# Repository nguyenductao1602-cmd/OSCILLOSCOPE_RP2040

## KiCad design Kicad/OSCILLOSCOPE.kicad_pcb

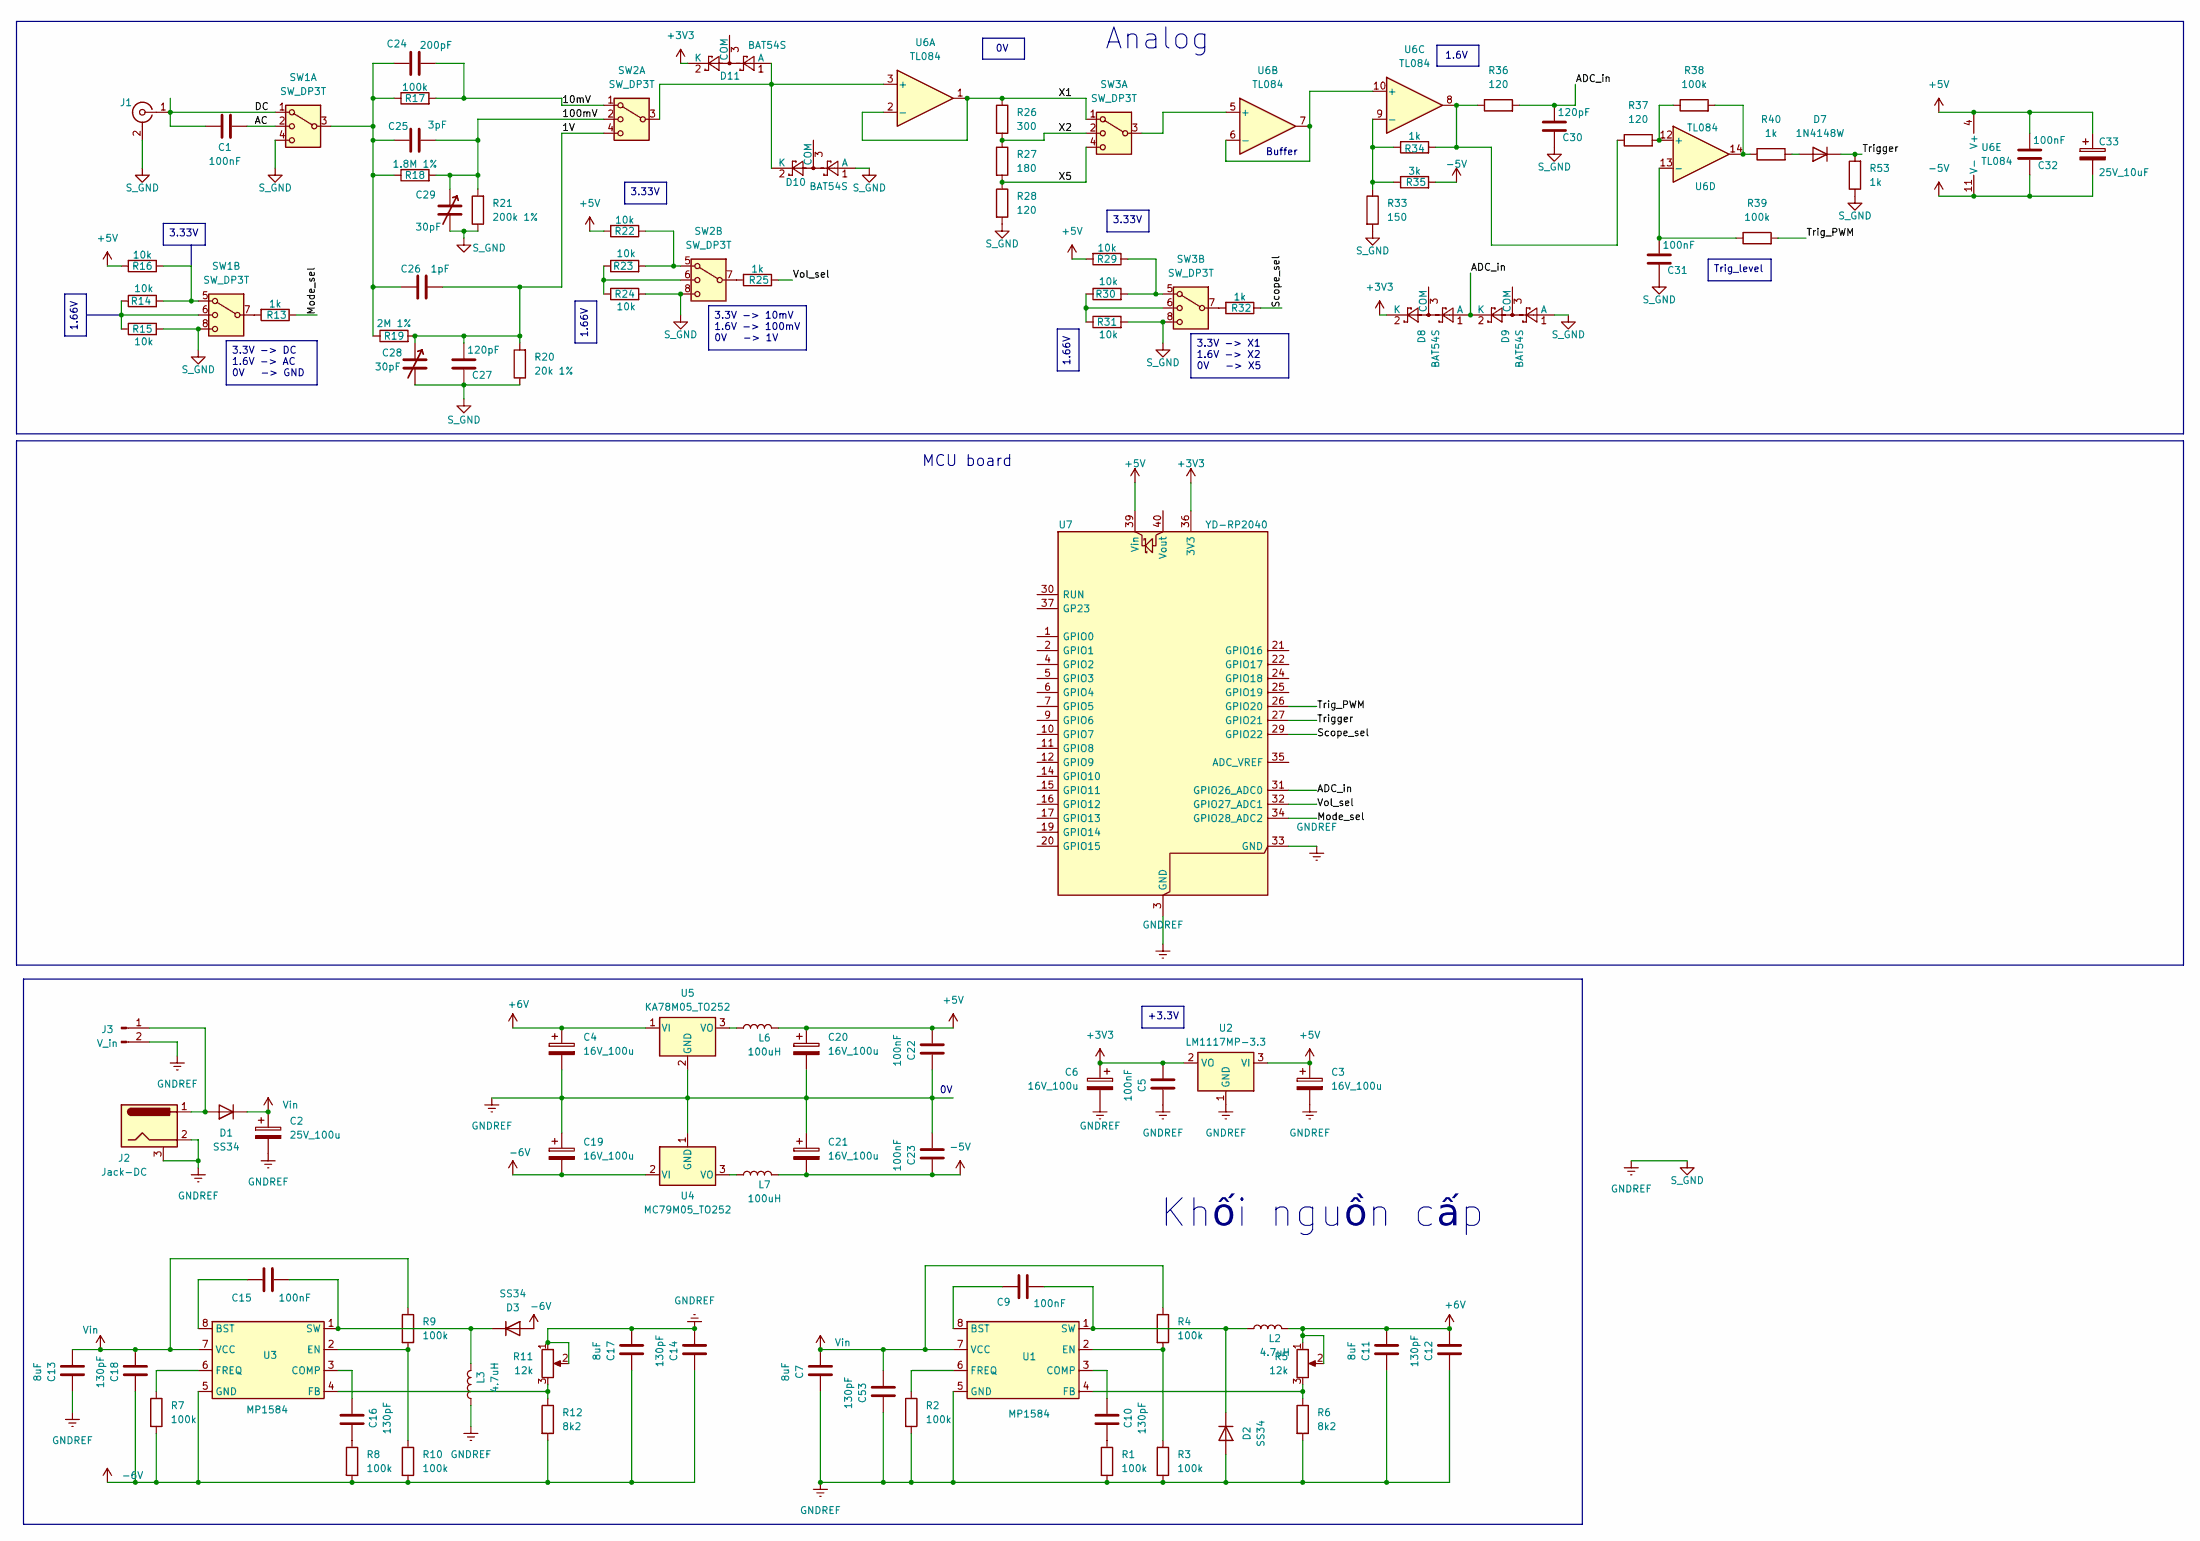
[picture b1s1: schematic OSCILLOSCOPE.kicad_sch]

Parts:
C1, C5, C22, C23, C31, C32: 100nF; C_0805_2012Metric
C2: 25V_100u; CP_Elec_6.3x7.7
C3, C4, C6, C19, C20, C21: 16V_100u; CP_Elec_6.3x7.7
C7, C11, C13, C17: 8uF; C_1206_3216Metric
C9, C15: 100nF; C_0402_1005Metric
C10, C12, C14, C16, C18, C53: 130pF; C_0402_1005Metric
C24: 200pF; C_0805_2012Metric
C25: 3pF; C_0805_2012Metric
C26: 1pF; C_0805_2012Metric
C27, C30: 120pF; C_0805_2012Metric
C28, C29: 30pF; C_Trimmer_Murata_TZC3
C33: 25V_10uF; CP_Elec_4x5.4
D1, D2, D3: SS34; D_SMA
D7: 1N4148W; D_SOD-123
D8, D9, D10, D11: BAT54S; SOT-23
J1: Conn_Coaxial; BNC_Amphenol_B6252HB-NPP3G-50_Horizontal
J2: Jack-DC; BarrelJack_CUI_PJ-102AH_Horizontal
J3: V_in; PinHeader_1x02_P2.54mm_Vertical
L2, L3: 4.7uH; L_Bourns_SRN6045TA
L6, L7: 100uH; L_Bourns_SRN6045TA
R1, R2, R3, R4, R7, R8, R9, R10: 100k; R_0402_1005Metric
R5, R11: 12k; Potentiometer_Bourns_TC33X_Vertical
R6, R12: 8k2; R_0402_1005Metric
R13, R25, R32, R34, R40, R53: 1k; R_0805_2012Metric
R14, R15, R16, R22, R23, R24, R29, R30, R31: 10k; R_0805_2012Metric
R17, R38, R39: 100k; R_0805_2012Metric
R18: 1.8M 1%; R_0805_2012Metric
R19: 2M 1%; R_0805_2012Metric
R20: 20k 1%; R_0805_2012Metric
R21: 200k 1%; R_0805_2012Metric
R26: 300; R_0805_2012Metric
R27: 180; R_0805_2012Metric
R28, R36, R37: 120; R_0805_2012Metric
R33: 150; R_0805_2012Metric
R35: 3k; R_0805_2012Metric
SW1, SW2, SW3: SW_DP3T; SW_DP3T_SS23D07_THT_TopActuator
U1, U3: MP1584; MP1584EN_SOIC8E_EP_GND5
U2: LM1117MP-3.3; SOT-223-3_TabPin2
U4: MC79M05_TO252; TO-252-2
U5: KA78M05_TO252; TO-252-2
U6: TL084; SOIC-14_3.9x8.7mm_P1.27mm
U7: YD-RP2040; Module_YD-RP2040

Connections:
+3V3: C5.2, C6.1, D8.2 (K), D11.2 (K), U2.2 (VO), U7.36 (3V3)
+5V: C3.1, C20.1, C22.2, C32.2, C33.1, L6.2, R16.2, R22.2, R29.2, U2.3 (VI), U6.4 (V+), U7.39 (Vin)
+6V: C4.1, C11.2, C12.2, L2.2, R5.1, R5.2, U5.1 (VI)
-5V: C21.2, C23.1, C32.1, C33.2, L7.2, R35.2, U6.11 (V-)
-6V: C14.1, C17.1, C18.1, C19.2, D3.2 (A), R7.2, R8.2, R10.2, R12.2, U3.5 (GND), U4.2 (VI)
/1V: C26.2, C27.2, C28.1, R19.2, R20.2, SW2.4
/10mV: C24.2, R17.2, SW2.1
/100mV: C25.2, C29.1, R18.2, R21.2, SW2.2
/AC: C1.2, SW1.2
/ADC_in: C30.2, D8.1 (A), D9.2 (K), R36.2, U7.31 (GPIO26_ADC0)
/DC: C1.1, J1.1 (In), SW1.1
/Mode_sel: R13.1, U7.34 (GPIO28_ADC2)
/Scope_sel: R32.1, U7.29 (GPIO22)
/Trig_PWM: R39.2, U7.26 (GPIO20)
/Trigger: D7.1 (K), R53.2, U7.27 (GPIO21)
/Vol_sel: R25.1, U7.32 (GPIO27_ADC1)
/X1: R26.1, SW3.1, U6.1, U6.2 (-)
/X2: R26.2, R27.1, SW3.2
/X5: R27.2, R28.1, SW3.4
GNDREF: C2.2, C3.2, C4.2, C5.1, C6.2, C7.1, C11.1, C12.1, C13.1, C14.2, C17.2, C19.1, C20.2, C21.1, C22.1, C23.2, C27.1, C28.2, C29.2, C30.1, C31.1, C53.1, D2.2 (A), D9.1 (A), D10.1 (A), J1.2 (Ext), J2.2, J2.3, J3.2, L3.1, R1.2, R2.2, R3.2, R6.2, R11.1, R11.2, R15.2, R20.1, R21.1, R24.2, R28.2, R31.2, R33.2, R53.1, SW1.4, SW1.8, SW2.8, SW3.8, U1.5 (GND), U2.1 (GND), U4.1 (GND), U5.2 (GND), U7.3 (GND), U7.8 (GND), U7.13 (GND), U7.18 (GND), U7.23 (GND), U7.28 (GND), U7.33 (GND), U7.38 (GND)
unnamed: C10.2, R1.1
unnamed: C16.2, R8.1
unnamed: C24.1, C25.1, C26.1, R17.1, R18.1, R19.1, SW1.3
unnamed: D1.2 (A), J2.1, J3.1
unnamed: C9.1, D2.1 (K), L2.1, U1.1 (SW)
unnamed: C15.1, D3.1 (K), L3.2, U3.1 (SW)
unnamed: D7.2 (A), R40.2
unnamed: D10.2 (K), D11.1 (A), SW2.3, U6.3 (+)
unnamed: R13.2, SW1.7
unnamed: R14.1, R15.1, SW1.6
unnamed: R14.2, R16.1, SW1.5
unnamed: R22.1, R23.2, SW2.5
unnamed: R23.1, R24.1, SW2.6
unnamed: R25.2, SW2.7
unnamed: R29.1, R30.2, SW3.5
unnamed: R30.1, R31.1, SW3.6
unnamed: R32.2, SW3.7
unnamed: R34.2, R36.1, R37.1, U6.8
unnamed: R38.2, R40.1, U6.14
unnamed: C9.2, U1.8 (BST)
unnamed: C10.1, U1.3 (COMP)
unnamed: R3.1, R4.2, U1.2 (EN)
unnamed: R5.3, R6.1, U1.4 (FB)
unnamed: R2.1, U1.6 (FREQ)
unnamed: C15.2, U3.8 (BST)
unnamed: C16.1, U3.3 (COMP)
unnamed: R9.2, R10.1, U3.2 (EN)
unnamed: R11.3, R12.1, U3.4 (FB)
unnamed: R7.1, U3.6 (FREQ)
unnamed: L7.1, U4.3 (VO)
unnamed: L6.1, U5.3 (VO)
unnamed: SW3.3, U6.5 (+)
unnamed: U6.6 (-), U6.7, U6.10 (+)
unnamed: R33.1, R34.1, R35.1, U6.9 (-)
unnamed: R37.2, R38.1, U6.12 (+)
unnamed: C31.2, R39.1, U6.13 (-)
Vin: C2.1, C7.2, C13.2, C18.2, C53.2, D1.1 (K), R4.1, R9.1, U1.7 (VCC), U3.7 (VCC)

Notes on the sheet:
1.6V
Buffer
Analog
Khối nguồn cấp
MCU board
Trig_level
3.33V
1.66V
3.3V -> DC 1.6V -> AC 0V -> GND
+3.3V
3.3V -> X1 1.6V -> X2 0V -> X5
3.3V -> 10mV 1.6V -> 100mV 0V -> 1V

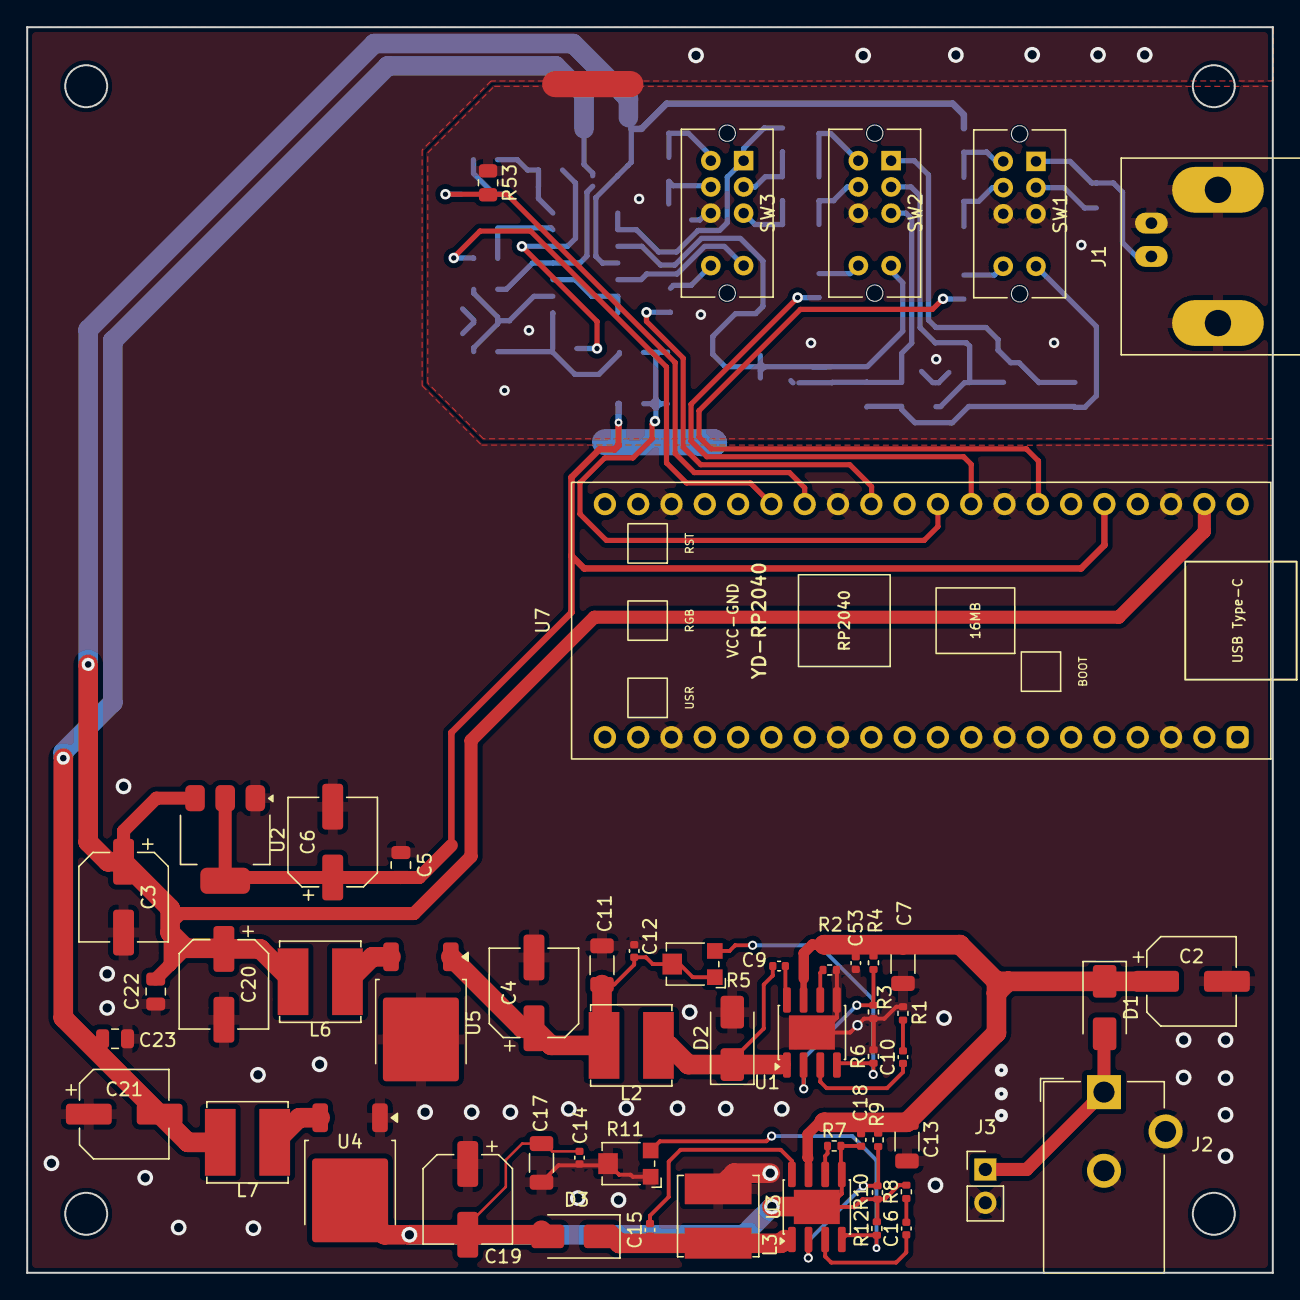
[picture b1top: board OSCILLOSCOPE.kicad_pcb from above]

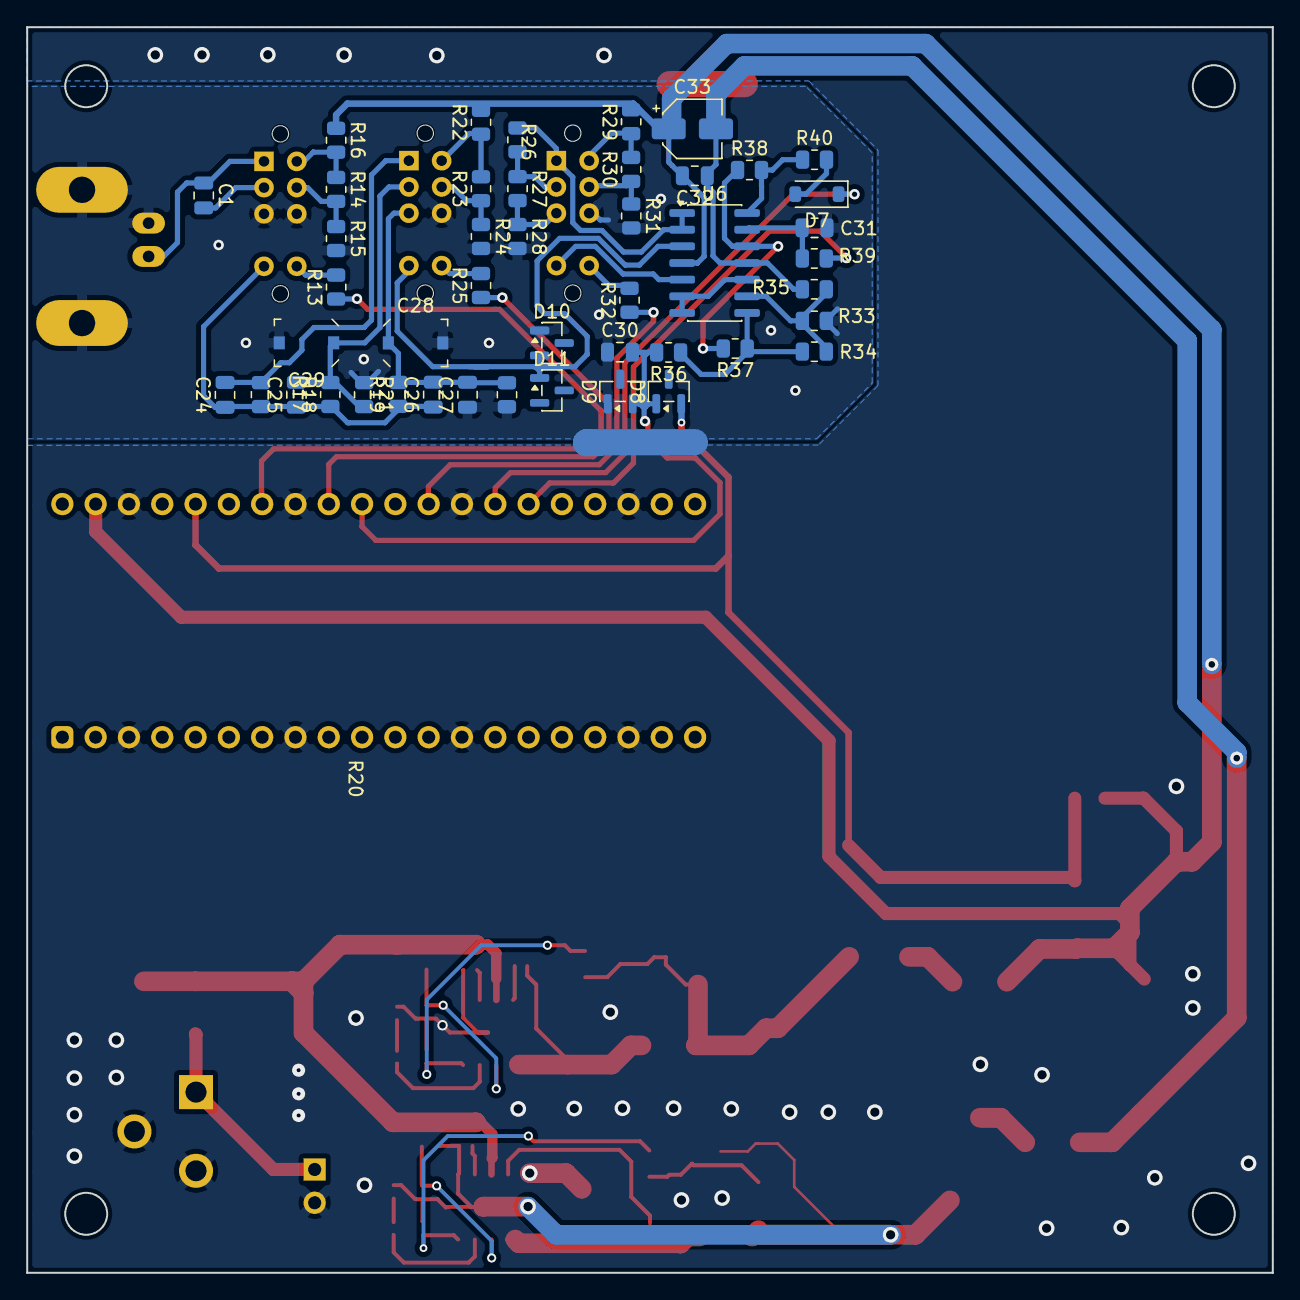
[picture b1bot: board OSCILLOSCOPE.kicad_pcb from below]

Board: 2 copper layers, 95.0 x 95.0 mm, 99 parts (45 on the bottom side), 57 nets.
